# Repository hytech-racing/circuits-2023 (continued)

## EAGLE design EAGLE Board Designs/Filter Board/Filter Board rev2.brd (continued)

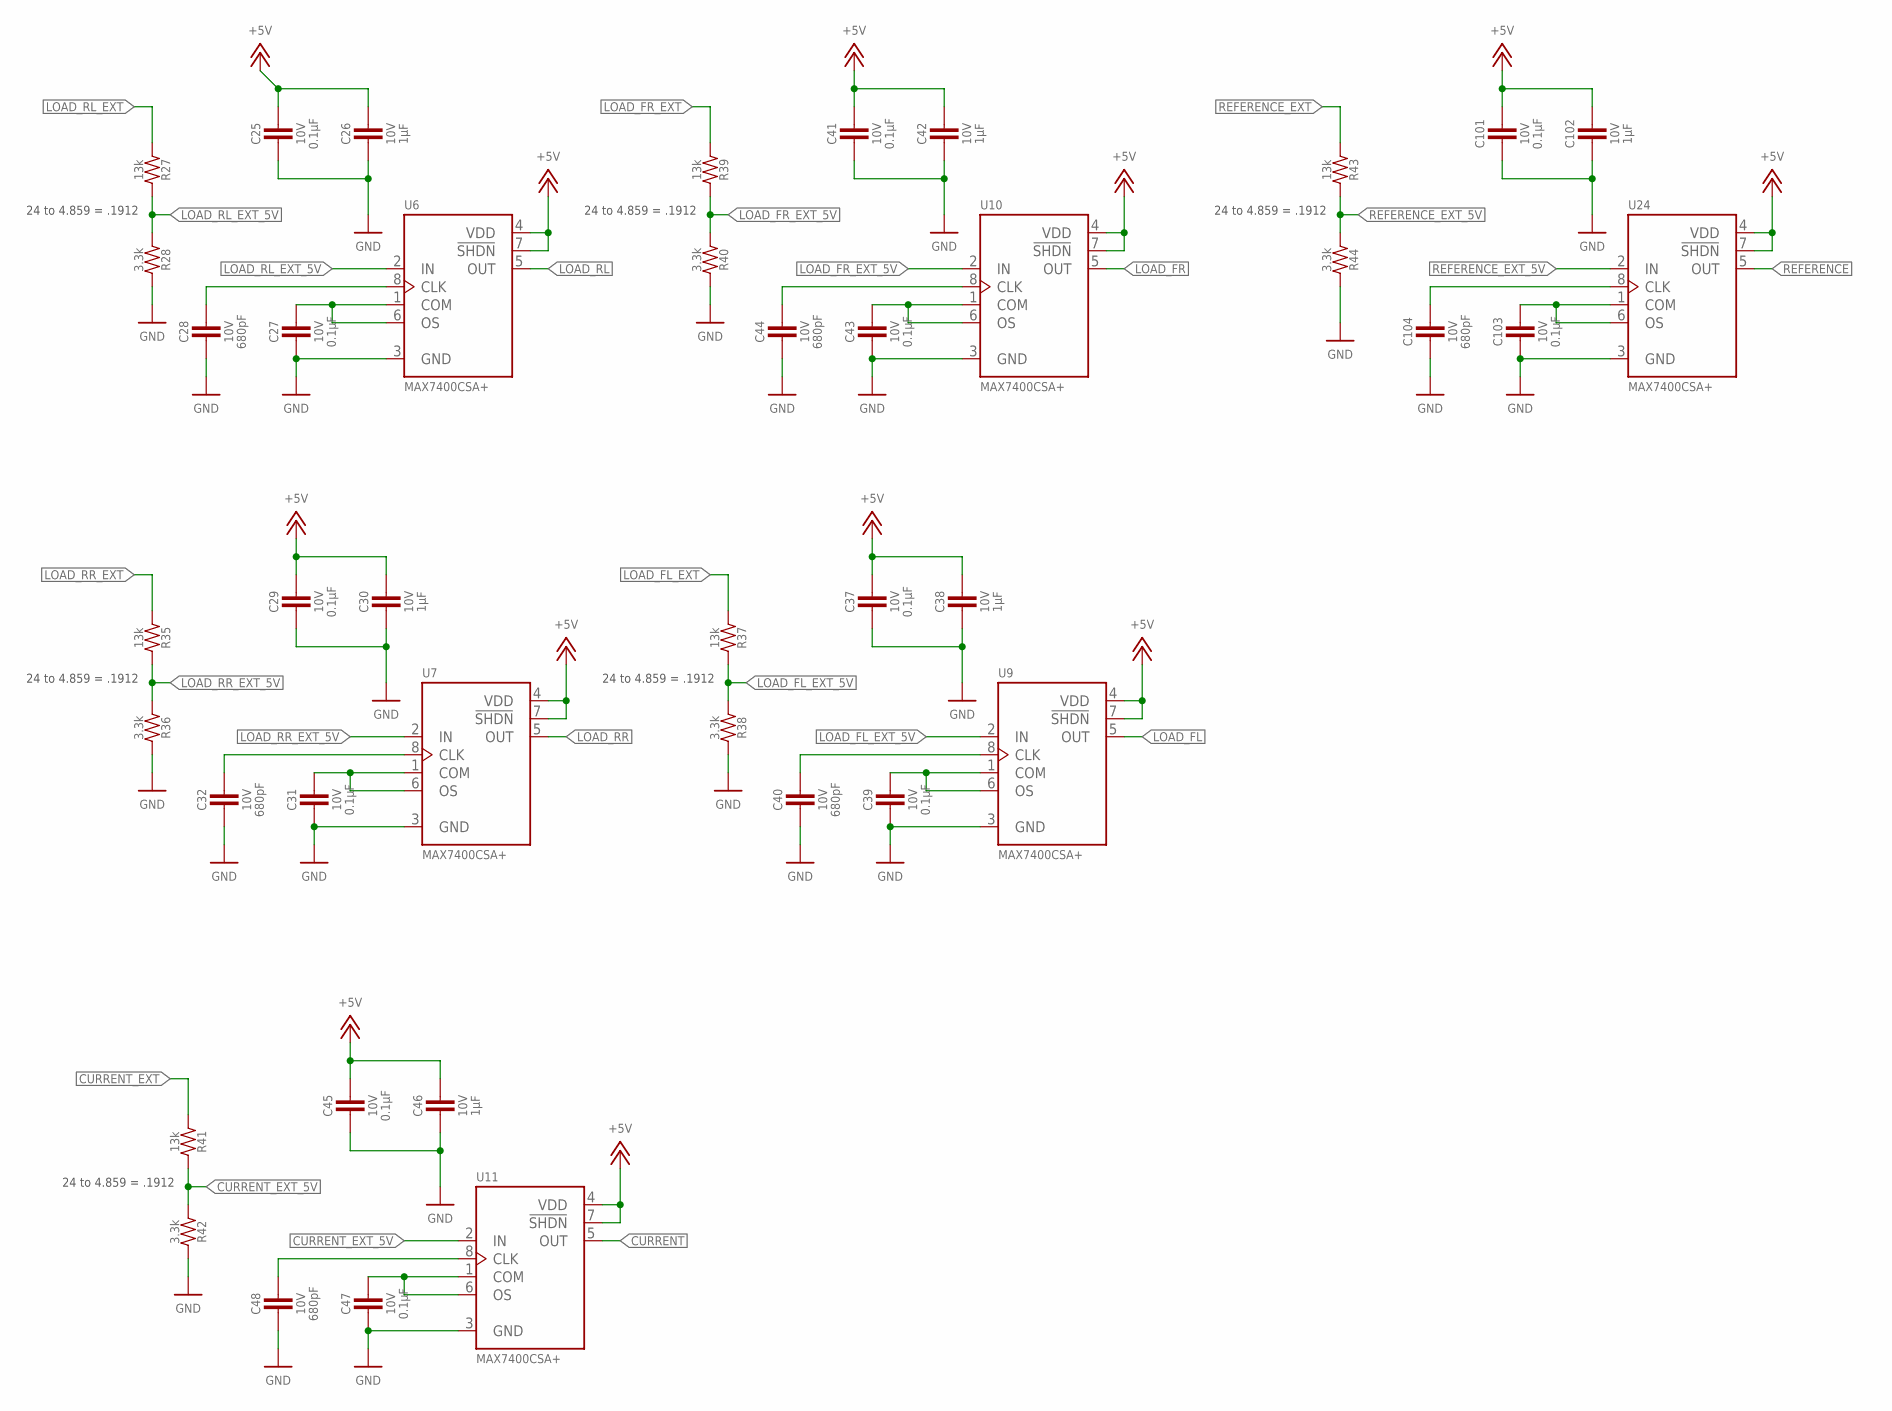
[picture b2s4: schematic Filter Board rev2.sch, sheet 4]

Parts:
C25, C27, C29, C31, C37, C39, C41, C43, C45, C47, C101, C103: CAPACITOR_0603_10V_0.1UF; 0603-CAP
C26, C30, C38, C42, C46, C102: CAPACITOR_0603_10V_1UF; 0603-CAP
C28, C32, C40, C44, C48, C104: CAPACITOR_0603_10V_680PF; 0603-CAP
R27, R35, R37, R39, R41, R43: RESISTOR_0603_13K; 0603-RES
R28, R36, R38, R40, R42, R44: RESISTOR_0603_3.3K; 0603-RES
U6, U7, U9, U10, U11, U24: MAX7400; SOIC-08(NARROW,0.15")

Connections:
+5V: C25.1, C26.1, C29.1, C30.1, C37.1, C38.1, C41.1, C42.1, C45.1, C46.1, C101.1, C102.1, U6.4 (VDD), U6.7 (!SHDN), U7.4 (VDD), U7.7 (!SHDN), U9.4 (VDD), U9.7 (!SHDN), U10.4 (VDD), U10.7 (!SHDN), U11.4 (VDD), U11.7 (!SHDN), U24.4 (VDD), U24.7 (!SHDN); also elsewhere on the board
CURRENT: U11.5 (OUT); also elsewhere on the board
CURRENT_EXT: R41.1; also elsewhere on the board
CURRENT_EXT_5V: R41.2, R42.1, U11.2 (IN)
GND: C25.2, C26.2, C27.2, C28.2, C29.2, C30.2, C31.2, C32.2, C37.2, C38.2, C39.2, C40.2, C41.2, C42.2, C43.2, C44.2, C45.2, C46.2, C47.2, C48.2, C101.2, C102.2, C103.2, C104.2, R28.2, R36.2, R38.2, R40.2, R42.2, R44.2, U6.3 (GND), U7.3 (GND), U9.3 (GND), U10.3 (GND), U11.3 (GND), U24.3 (GND); also elsewhere on the board
LOAD_FL: U9.5 (OUT); also elsewhere on the board
LOAD_FL_EXT: R37.1; also elsewhere on the board
LOAD_FL_EXT_5V: R37.2, R38.1, U9.2 (IN)
LOAD_FR: U10.5 (OUT); also elsewhere on the board
LOAD_FR_EXT: R39.1; also elsewhere on the board
LOAD_FR_EXT_5V: R39.2, R40.1, U10.2 (IN)
LOAD_RL: U6.5 (OUT); also elsewhere on the board
LOAD_RL_EXT: R27.1; also elsewhere on the board
LOAD_RL_EXT_5V: R27.2, R28.1, U6.2 (IN)
LOAD_RR: U7.5 (OUT); also elsewhere on the board
LOAD_RR_EXT: R35.1; also elsewhere on the board
LOAD_RR_EXT_5V: R35.2, R36.1, U7.2 (IN)
unnamed: C28.1, U6.8 (CLK)
unnamed: C27.1, U6.1 (COM), U6.6 (OS)
unnamed: C32.1, U7.8 (CLK)
unnamed: C31.1, U7.1 (COM), U7.6 (OS)
unnamed: C40.1, U9.8 (CLK)
unnamed: C39.1, U9.1 (COM), U9.6 (OS)
unnamed: C44.1, U10.8 (CLK)
unnamed: C43.1, U10.1 (COM), U10.6 (OS)
unnamed: C48.1, U11.8 (CLK)
unnamed: C47.1, U11.1 (COM), U11.6 (OS)
unnamed: C104.1, U24.8 (CLK)
unnamed: C103.1, U24.1 (COM), U24.6 (OS)
REFERENCE: U24.5 (OUT); also elsewhere on the board
REFERENCE_EXT: R43.1; also elsewhere on the board
REFERENCE_EXT_5V: R43.2, R44.1, U24.2 (IN)

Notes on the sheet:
24 to 4.859 = .1912

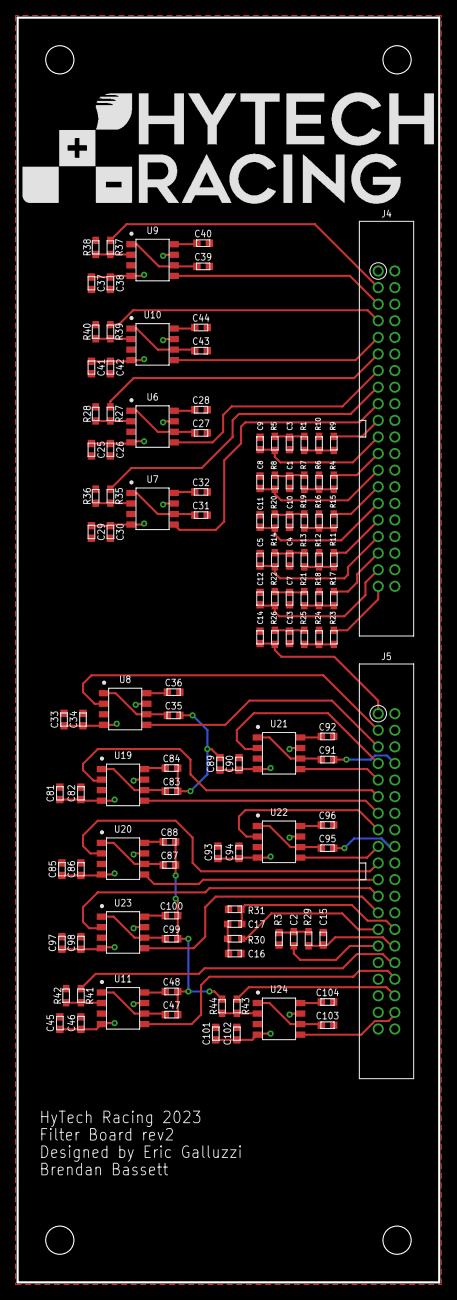
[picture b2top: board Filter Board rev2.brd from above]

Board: 2 copper layers, 50.8 x 152.4 mm, 124 parts (1 on the bottom side), 86 nets.

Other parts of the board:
U$1, U$2, U$3, U$4: MOUNTING_M3
U$5, U$6: LOGO_HYTECH_LARGE

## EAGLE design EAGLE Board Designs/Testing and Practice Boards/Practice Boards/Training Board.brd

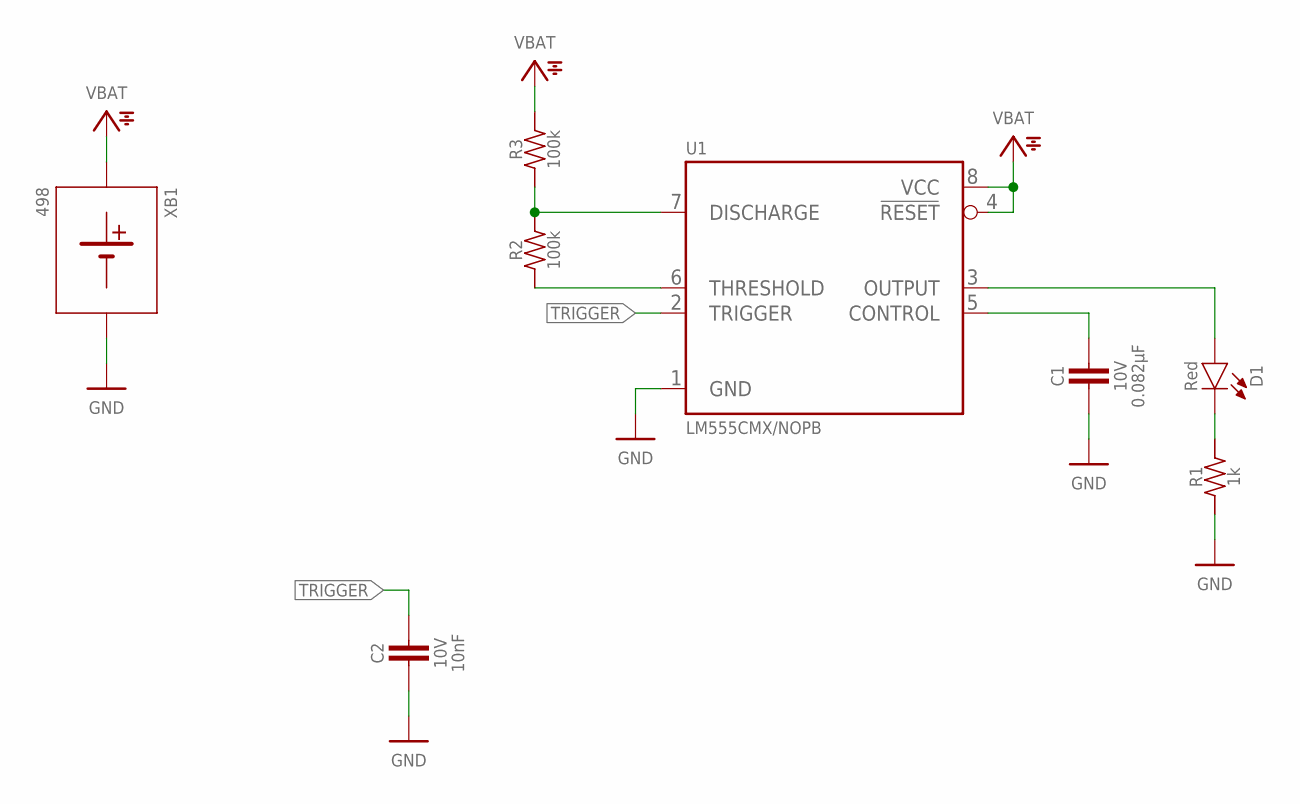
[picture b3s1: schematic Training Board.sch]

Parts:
C1: CAPACITOR_0603_10V_0.082UF; 0603-CAP
C2: CAPACITOR_0603_10V_10NF; 0603-CAP
D1: LED_0603_RED; 0603-LED
R1: RESISTOR_0603_1K; 0603-RES
R2, R3: RESISTOR_0603_100K; 0603-RES
U1: LM555; SOIC-08(NARROW,0.15")
XB1: BATTERY_HOLDER_KEYSTONE_498; 498

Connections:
GND: C1.2, C2.2, R1.1, U1.1 (GND), XB1.2 (MINUS)
unnamed: C1.1, U1.5 (CONTROL)
unnamed: D1.2 (A), U1.3 (OUTPUT)
unnamed: D1.1 (C), R1.2
unnamed: R2.2, R3.1, U1.7 (DISCHARGE)
unnamed: R2.1, U1.6 (THRESHOLD)
TRIGGER: C2.1, U1.2 (TRIGGER)
VBAT: R3.2, U1.4 (!RESET), U1.8 (VCC), XB1.1 (PLUS)

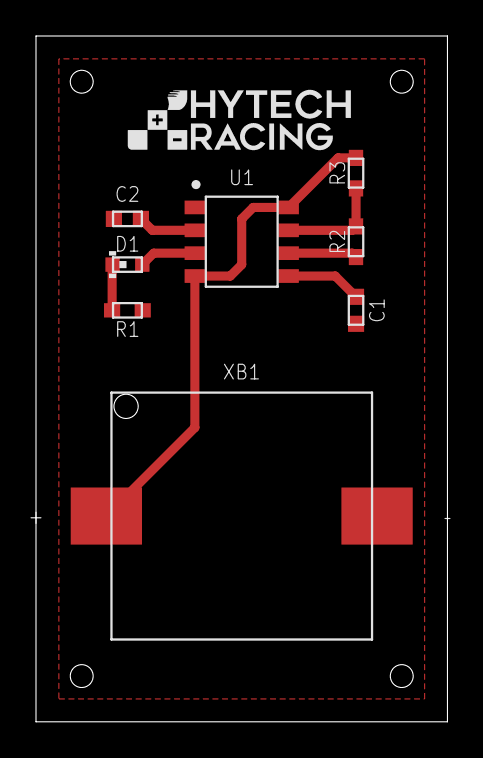
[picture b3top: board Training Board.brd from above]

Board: 2 copper layers, 22.9 x 38.1 mm, 9 parts (0 on the bottom side), 8 nets.

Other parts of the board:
U$1: LOGO_HYTECH_SMALL

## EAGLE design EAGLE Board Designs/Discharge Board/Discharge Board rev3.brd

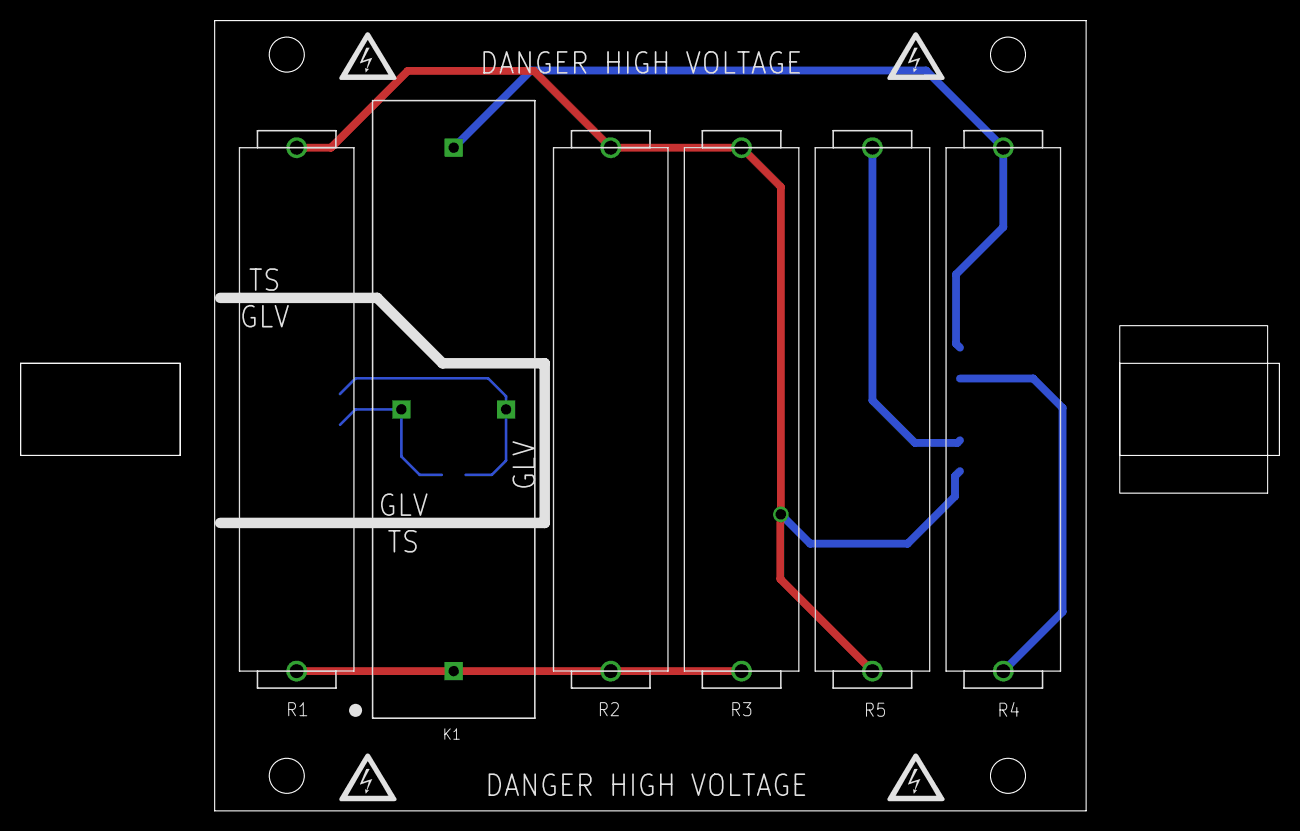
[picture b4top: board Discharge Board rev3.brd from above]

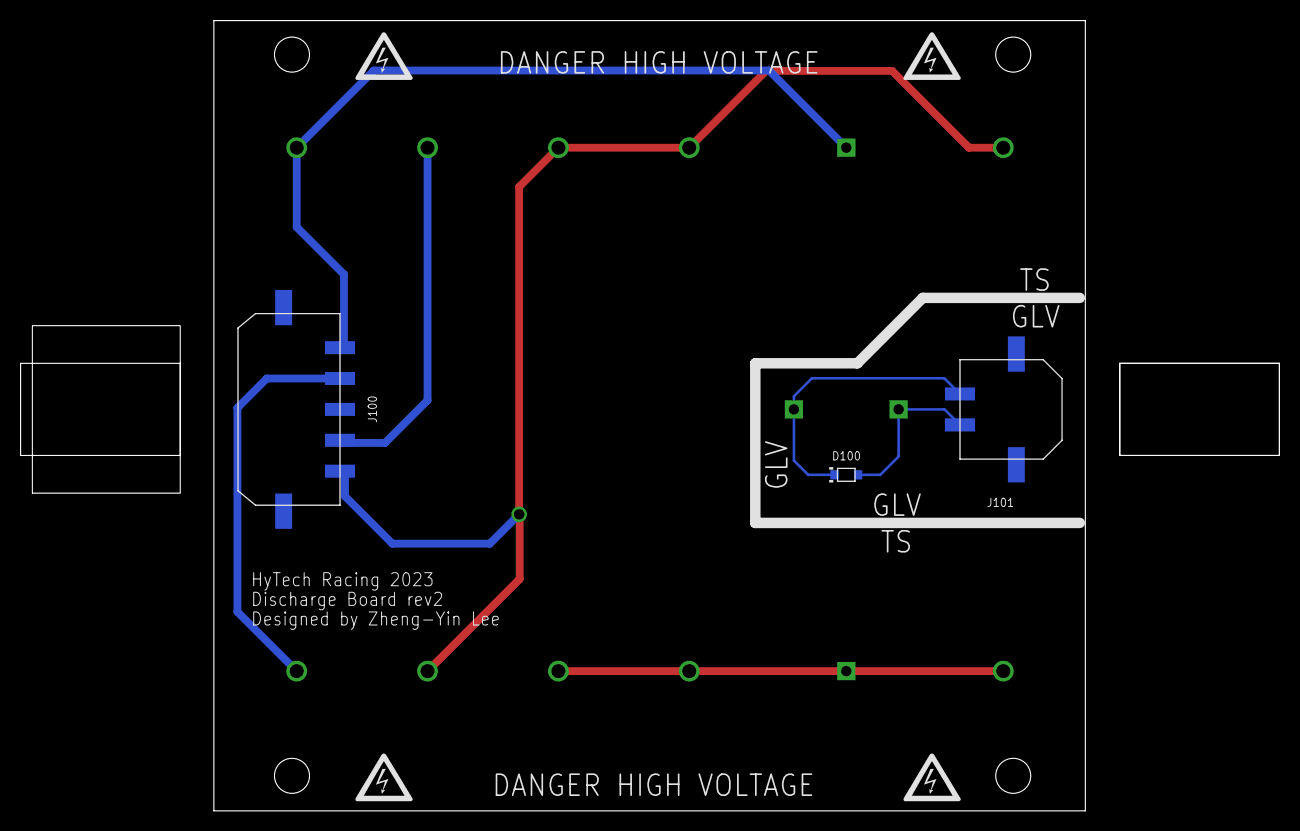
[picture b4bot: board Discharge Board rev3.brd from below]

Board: 2 copper layers, 122.2 x 76.7 mm, 28 parts (7 on the bottom side), 7 nets.

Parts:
D100: SCHOTTKY_SOD323_60V; SOD-323
J100: CONNECTOR-5_MICRO_R5S_; MOLEX_MICROFIT_SMD_RIGHTANGLE_05_SINGLE
J101: CONNECTOR-2_MICROFIT_SMD_RIGHTANGLE_02_SINGLE_BLA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; MOLEX_MICROFIT_SMD_RIGHTANGLE_02_SINGLE
K1: RELAY_SPST_NC_POLARIZED_D_24; D
R1, R2, R3, R4, R5: RESISTOR_B20-SHORTENED_15K; B20-SHORTENED
U$1, U$2, U$5: GLV
U$3, U$4: TS
U$6, U$19: DANGER_HIGH_VOLTAGE
U$7, U$8, U$9, U$10, U$11, U$12, U$13, U$14: HV_MEDIUM
U$15, U$16, U$17, U$18: MOUNTING_M3

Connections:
GND: D100.A, J101.2, K1.3
unnamed: J100.2, R5.2
unnamed: J100.4, R4.1
unnamed: K1.1, R1.2, R2.2, R3.2
SHDN: D100.C, J101.1, K1.4
TS+UNFUSED: J100.5, K1.2, R4.2
TS-UNFUSED: J100.1, R1.1, R2.1, R3.1, R5.1

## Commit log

2022-09-16 created training boards
2022-09-16 fixed silkscreen
2022-11-01 playground filter board schematics
2022-11-02 progress
2022-11-03 Prototype filter schematic
    my eagle is scuffed :(
2022-11-03 Updated Filter Board Schematic
2022-11-04 added second order rc filter
2022-11-08 Grouped components together!
2022-11-08 Fixed width and added ground plane!
2022-11-11 Placing things on Board!
2022-11-11 I suck at this
2022-11-11 fixed wire widths
2022-11-13 Update Filter Board
2022-11-14 Next Step: Compact
2022-11-14 compact filter
2022-11-14 more!
2022-11-15 I'll take another look tomorrow
    Improved filter and wire alignment
2022-11-16 Large Logo for Large Frequencies
    to be filtered later...
2022-11-17 quick fix
2022-11-17 inverted design
2022-11-17 I am awful at eagle
2022-11-18 GOt it
2022-11-18 embarassing
2022-11-18 vector -> proportional
2022-11-18 Updated for HyTech Default DRC
2022-11-20 ordering file
2022-12-05 simplified passive filters
2022-12-05 fixed drc
2022-12-11 first progress
2022-12-11 enough for two strain gauges
    waiting to find datasheet on infrared sensors.
2022-12-12 updated passive filters and routing
2022-12-12 passes drc as is
2022-12-12 labels for all passive components visible
2022-12-23 10 strain gauges and aero uart, passes drc
2023-03-12 moved drill holes
2023-04-07 track testing board
